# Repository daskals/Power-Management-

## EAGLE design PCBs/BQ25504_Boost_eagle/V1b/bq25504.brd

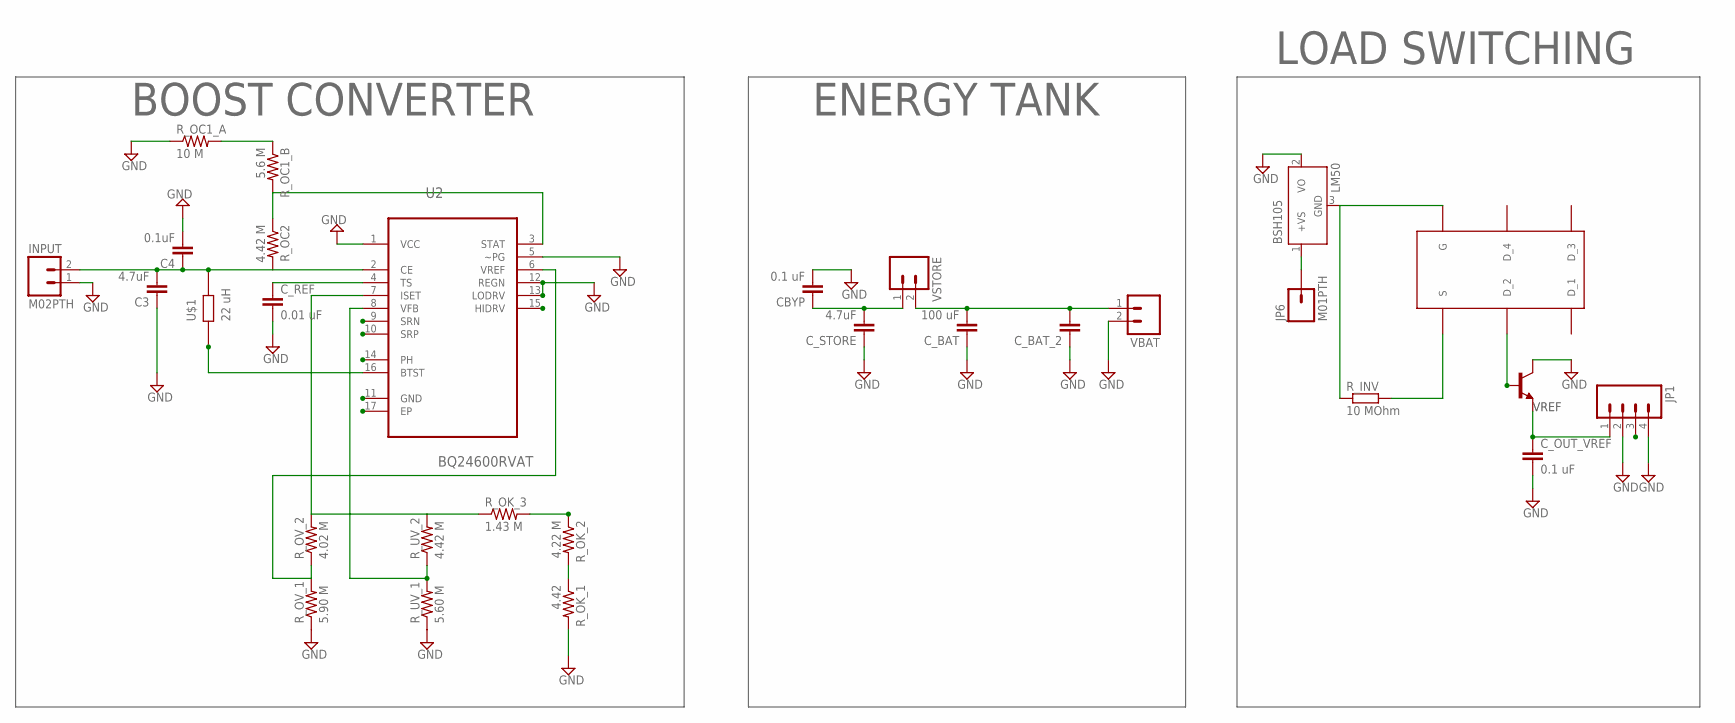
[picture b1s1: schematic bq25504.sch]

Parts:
BSH105: LM50; SOT23
BSH207: BSH_105_NMOS_DEV; SOT457
C3: 4.7uF; 0805
C4: 0.1uF; 0805
CBYP: 0.1 uF; 0805
C_BAT: 100 uF; 0805
C_BAT_2: CAP1210; 1210
C_OUT_VREF: 0.1 uF; 0603-CAP
C_REF: 0.01 uF; 0805
C_STORE: 4.7uF; 0805
INPUT: M02PTH; 1X02
JP1: M04LOCK; 1X04_LOCK
JP6: M01PTH; 1X01
R_INV: 10 MOhm; R0603
R_OC1_A: 10 M; 0805
R_OC1_B: 5.6 M; 0805
R_OC2: 4.42 M; 0805
R_OK_1: 4.42; 0805
R_OK_2: 4.22 M; 0805
R_OK_3: 1.43 M; 0805
R_OV_1: 5.90 M; 0805
R_OV_2: 4.02 M; 0805
R_UV_1: 5.60 M; 0805
R_UV_2: 4.42 M; 0805
U2: BQ24600RVAT; QFN50P350X350X100-17N
U$1: 22 uH; LPS4018
VBAT: M02PTH; 1X02
VREF_1.8: TRANSISTOR_NPNSOT23-3; SOT23-3
VSTORE: M02PTH; 1X02

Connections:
9_PIN: R_OK_2.1, R_OK_3.2, U2.9 (SRN)
10_PIN: R_OK_1.1, R_OK_2.2, U2.10 (SRP)
BAT_OK: BSH105.1 (+VS), JP6.1, U2.11 (GND)
BOOST_OUT: BSH207.2 (D_2), JP1.3, VREF_1.8.1 (B)
GND: BSH105.2 (VO), C3.1, C4.2, CBYP.2, C_BAT.1, C_BAT_2.1, C_OUT_VREF.2, C_REF.2, C_STORE.1, INPUT.1, JP1.2, JP1.4, R_OC1_A.1, R_OK_1.2, R_OV_1.1, R_UV_1.1, U2.1 (VCC), U2.5 (~PG), U2.12 (REGN), U2.13 (LODRV), VBAT.2, VREF_1.8.3 (C)
J: U2.16 (BTST), U$1.A
unnamed: C3.2, C4.1, INPUT.2, R_OC2.2, U2.2 (CE), U$1.B
unnamed: R_OV_1.2, R_OV_2.1, U2.6 (VREF)
unnamed: R_OC1_B.2, R_OC2.1, U2.3 (STAT)
unnamed: R_UV_1.2, R_UV_2.1, U2.8 (VFB)
unnamed: C_REF.1, U2.4 (TS)
unnamed: R_OC1_A.2, R_OC1_B.1
unnamed: C_OUT_VREF.1, JP1.1, VREF_1.8.2 (E)
unnamed: BSH105.3 (GND), BSH207.3 (G), R_INV.1
V_BAT: BSH207.4 (S), C_BAT.2, C_BAT_2.2, R_INV.2, U2.14 (PH), VBAT.1, VSTORE.2
V_STORE: CBYP.1, C_STORE.2, U2.15 (HIDRV), VSTORE.1
WIRE: R_OK_3.1, R_OV_2.2, R_UV_2.2, U2.7 (ISET)

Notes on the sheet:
VREF
BOOST CONVERTER
ENERGY TANK
LOAD SWITCHING

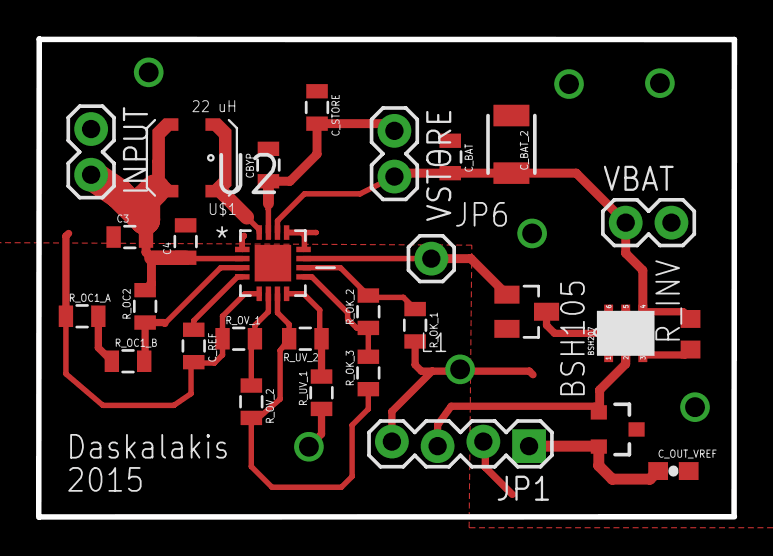
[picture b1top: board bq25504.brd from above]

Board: 2 copper layers, 38.7 x 26.6 mm, 29 parts (0 on the bottom side), 17 nets.

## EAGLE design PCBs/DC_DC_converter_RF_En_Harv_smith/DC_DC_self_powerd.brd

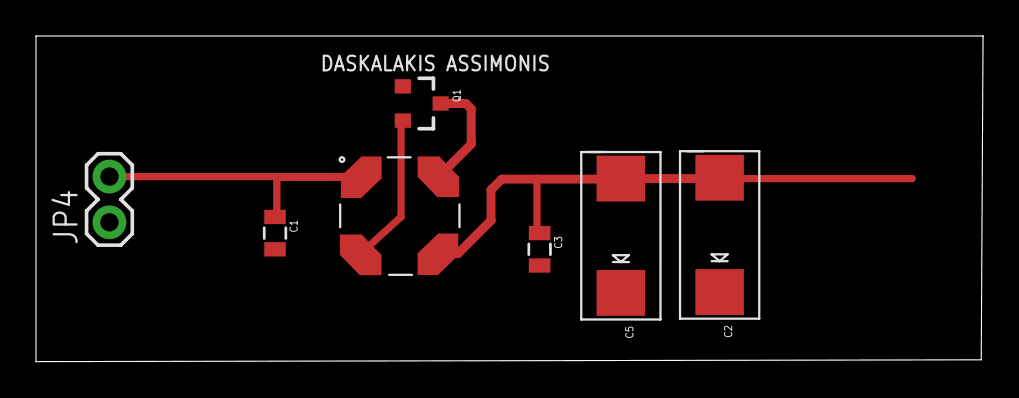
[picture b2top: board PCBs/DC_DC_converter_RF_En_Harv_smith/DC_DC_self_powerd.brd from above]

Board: 2 copper layers, 52.6 x 18.1 mm, 7 parts (0 on the bottom side), 5 nets.

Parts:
C1, C3: 0805
C2, C5: 220uF; EIA7343-31/D-R
JP4: 1X02
L1: 100:1; COILCRAFT_LPR6235
Q1: SOT23-3

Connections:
GND: C1.2, C2.+, C3.2, C5.+, JP4.1, Q1.1
unnamed: L1.P$4, Q1.3
unnamed: L1.P$2, Q1.2
unnamed: C2.-, C3.1, C5.-, L1.P$3
unnamed: C1.1, JP4.2, L1.P$1

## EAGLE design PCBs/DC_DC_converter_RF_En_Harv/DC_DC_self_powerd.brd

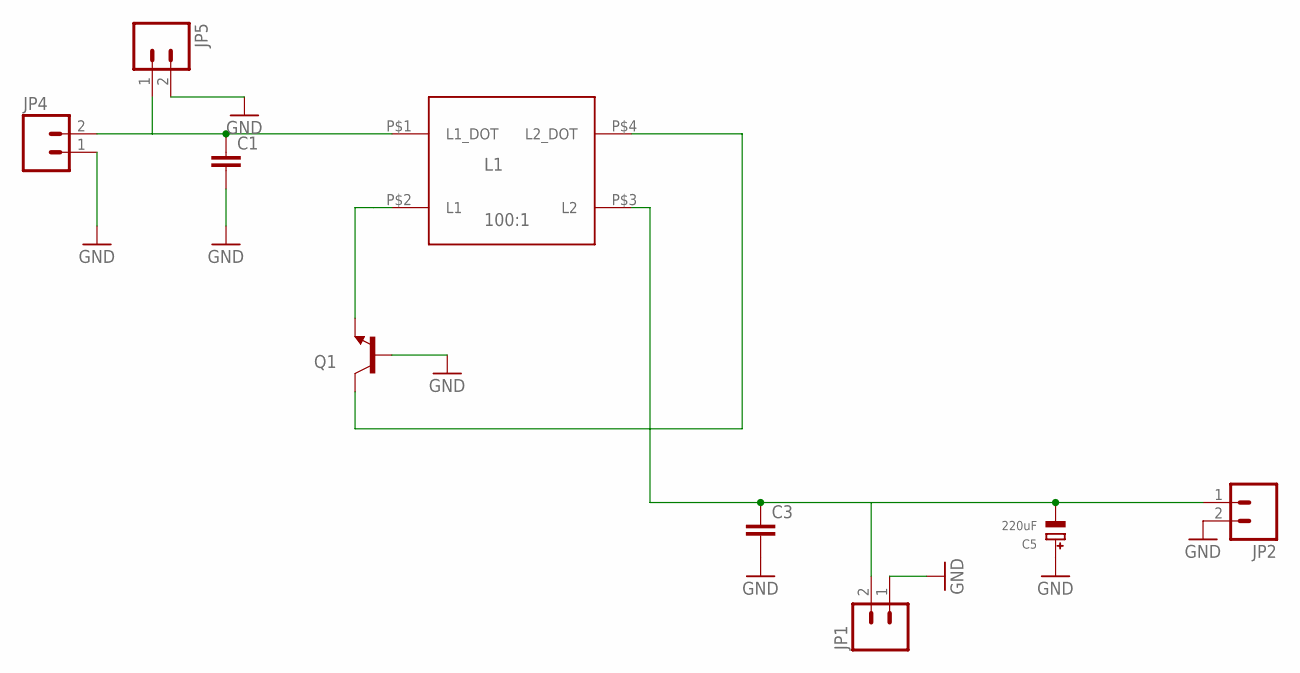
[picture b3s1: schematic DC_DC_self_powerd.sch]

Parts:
C1, C3: CAP0805; 0805
C5: 220uF; EIA7343-31/D-R
JP1, JP2, JP4, JP5: M02PTH; 1X02
L1: 100:1; COILCRAFT_LPR6235
Q1: TRANSISTOR_NPNSOT23-3; SOT23-3

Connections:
GND: C1.2, C3.2, C5.+, JP1.1, JP2.2, JP4.1, JP5.2, Q1.1 (B)
unnamed: L1.P$4 (L2_DOT), Q1.3 (C)
unnamed: L1.P$2 (L1), Q1.2 (E)
unnamed: C3.1, C5.-, JP1.2, JP2.1, L1.P$3 (L2)
unnamed: C1.1, JP4.2, JP5.1, L1.P$1 (L1_DOT)

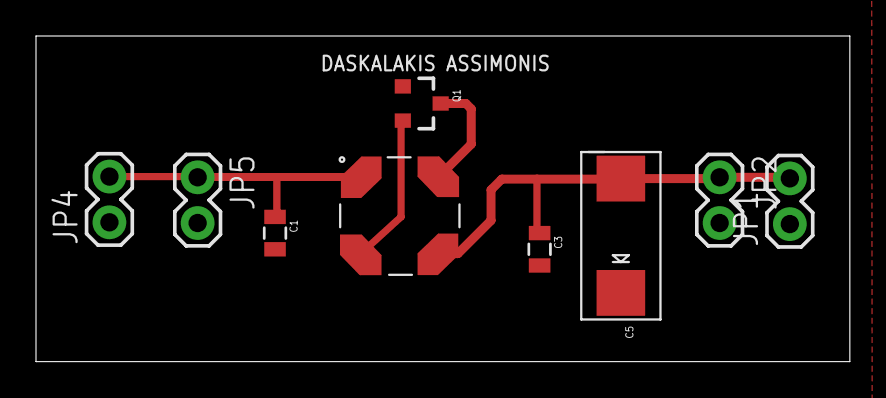
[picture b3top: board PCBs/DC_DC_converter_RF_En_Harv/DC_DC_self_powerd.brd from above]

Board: 2 copper layers, 45.2 x 18.1 mm, 9 parts (0 on the bottom side), 5 nets.

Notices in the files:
parts and their libraries:
SparkFun-Resistors: Licensing: CC v3.0 Share-Alike You are welcome to use this library for commercial purposes.
